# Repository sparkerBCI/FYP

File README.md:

# Brain Computer Interface Controlled, 3-D Printed Prosthetic Hand

This is an Electrical Engineering Final   Year Project by Samuel Parker, from the University of Newcastle.

### Scope
The project will attempt to conduct a real time frequency analysis of on-line EEG data. The frequency content will then be classified into "Hand Open" or "Hand Closed" using an appropriate classification algorithm. Once classified, the state will be used to control the servos in the 3D printed prosthetic hand. The goal of the project is to achieve realtime, neurally controlled grasping.

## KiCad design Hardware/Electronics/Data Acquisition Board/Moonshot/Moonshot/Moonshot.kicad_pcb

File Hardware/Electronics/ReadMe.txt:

A place to store electronics design files

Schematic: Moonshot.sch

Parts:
A1: Arduino_Nano_v2.x; Arduino_Nano
ADC1: ADS1299-Board
C1, C5: 10u; C_0603_1608Metric_Pad1.05x0.95mm_HandSolder
C2, C4: 1u; C_0603_1608Metric_Pad1.05x0.95mm_HandSolder
C3: 100n; C_0603_1608Metric_Pad1.05x0.95mm_HandSolder
D1: 7.5V; D_SMA_Handsoldering
J1: Barrel_Jack; BarrelJack_CUI_PJ-063AH_Horizontal
J2: Conn_01x06_Female; HC-05
J3, J4, J5, J6, J7, J8, J9, J10, J11: Conn_01x01_Male; DIN 42802-1
Q1: DMP2100U; SOT-23
R1: 33k; R_0603_1608Metric_Pad1.05x0.95mm_HandSolder
R2, R3, R4, R5: 1k; R_0603_1608Metric_Pad1.05x0.95mm_HandSolder
R6, R7, R8, R9: 2k; R_0603_1608Metric_Pad1.05x0.95mm_HandSolder
U2: MCP1755T-5002E_SOT223-5; SOT-223-6

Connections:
/+3V3: A1.17 (3V3), ADC1.5, ADC1.6
/+5V: C3.1, C4.1, C5.1, J2.5, U2.4
/BT_RX_3V3: A1.11 (D8), J2.3
/BT_TX_3V3: J2.2, R2.1, R6.1
/BT_TX_5V: A1.12 (D9), R2.2
/GND: A1.4 (GND), A1.29 (GND), ADC1.2, ADC1.8, C1.2, C2.2, C3.2, C4.2, C5.2, J1.2, J2.4, R1.2, R6.2, R7.2, R8.2, R9.2, U2.3, U2.5, U2.6
/LED: A1.6 (D3)
/MISO_3V3: A1.15 (D12), ADC1.11
/MOSI_3V3: ADC1.4, R4.1, R8.1
/MOSI_5V: A1.14 (D11), R4.2
/SCLK_3V3: ADC1.10, R3.1, R7.1
/SCLK_5V: A1.16 (D13), R3.2
/V+: A1.30 (VIN), ADC1.1, C1.1, C2.1, D1.1, Q1.2, U2.1, U2.2
/~CS_3V3: ADC1.9, R5.1, R9.1
/~CS_5V: A1.7 (D4), R5.2
/~DRDY_3V3: A1.9 (D6), ADC1.12
unnamed: ADC1.21, J11.1
unnamed: ADC1.22, J10.1
unnamed: ADC1.23, J9.1
unnamed: ADC1.24, J8.1
unnamed: ADC1.25, J7.1
unnamed: ADC1.26, J6.1
unnamed: ADC1.27, J5.1
unnamed: ADC1.28, J4.1
unnamed: ADC1.29, J3.1
unnamed: D1.2, Q1.1, R1.1
unnamed: J1.1, Q1.3

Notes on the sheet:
LED
GND
+5V
STATE

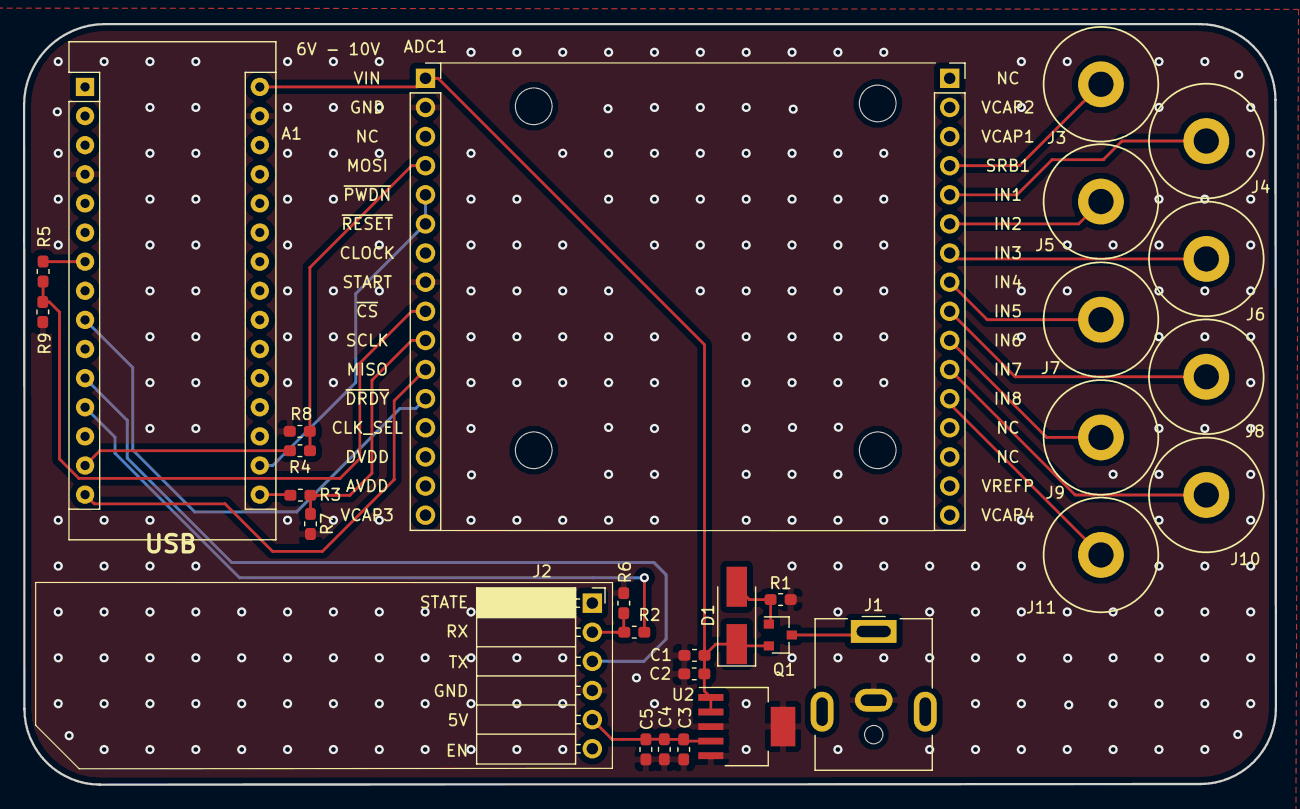
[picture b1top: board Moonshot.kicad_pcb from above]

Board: 2 copper layers, 109.2 x 66.3 mm, 34 parts (0 on the bottom side), 26 nets.

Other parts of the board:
 : MountingHole_3.2mm_M3
 #2,  #3,  #4: MountingHole_3.2mm_M3

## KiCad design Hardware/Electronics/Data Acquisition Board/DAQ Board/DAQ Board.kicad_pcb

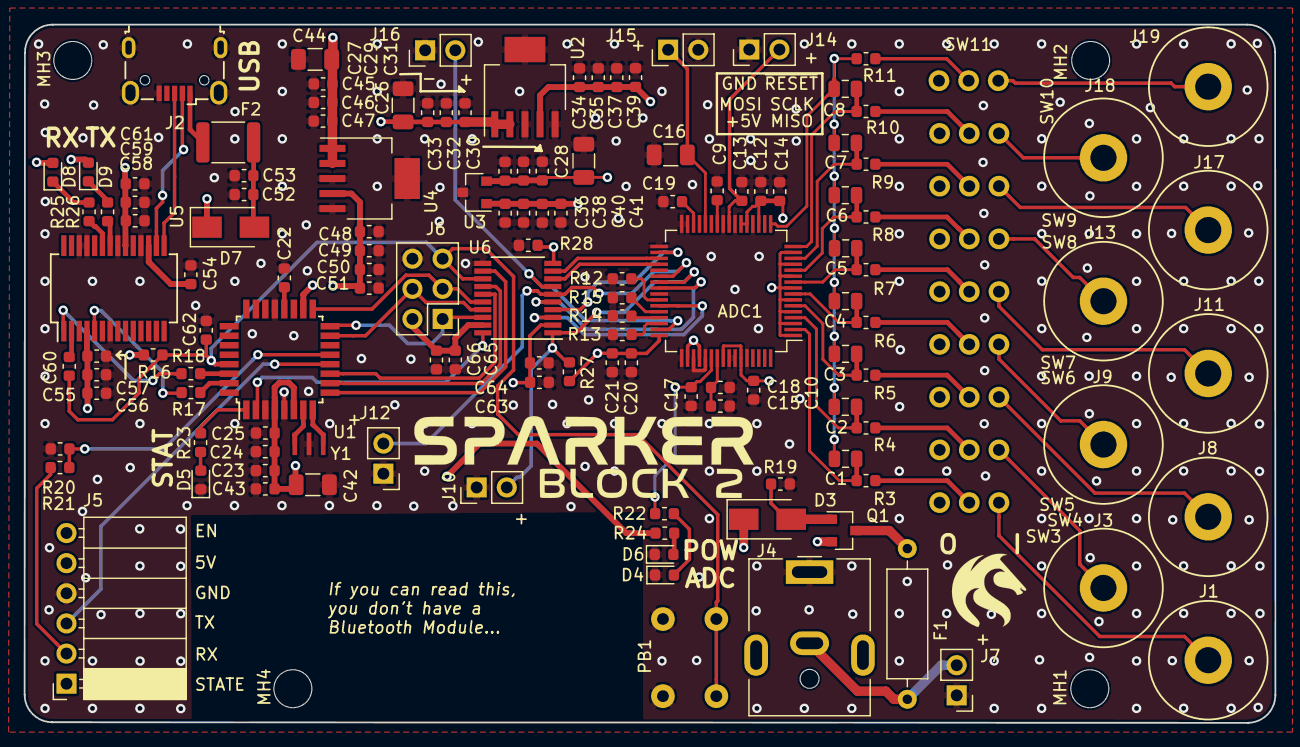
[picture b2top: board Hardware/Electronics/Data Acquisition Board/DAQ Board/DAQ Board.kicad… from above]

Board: 4 copper layers, 105.4 x 58.9 mm, 145 parts (0 on the bottom side), 84 nets.

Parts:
ADC1: ADS1299-8; TQFP-64_10x10mm_P0.5mm
C1, C2, C3, C4, C5, C6, C7, C8: 24nF; C_0805_2012Metric
C9, C10, C14, C17, C18, C19, C21, C23, C25: 1uF; C_0603_1608Metric
C12, C15, C20: 0.1uF; C_0603_1608Metric
C13, C27, C30, C39, C41, C43, C45, C51, C55, C61, C62: 10uF; C_0603_1608Metric
C16, C26, C28, C42, C44: 100uF; C_1206_3216Metric
C22, C29, C32, C37, C40, C46, C50, C53, C54, C56, C59, C60: 100nF; C_0603_1608Metric
C24, C52: 4.7uF; C_0603_1608Metric
C31, C33, C35, C38, C47, C49, C57, C58: 10nF; C_0603_1608Metric
C34, C36, C48: 1nF; C_0603_1608Metric
C63, C66: 100n; C_0603_1608Metric
C64, C65: 10n; C_0603_1608Metric
D3: 7.5V; D_SMA
D4, D6: LTST-C194TBKT; LED_0603_1608Metric
D5, D9: LTST-C191KGKT; LED_0603_1608Metric
D7: B130-13-F; D_SMA
D8: LTST-C191KRKT; LED_0603_1608Metric
F1: 025101.5MAT1L; R_Axial_DIN0309_L9.0mm_D3.2mm_P12.70mm_Horizontal
F2: MF-MSMF050-2; Fuse_1812_4532Metric
J1, J3, J8, J9, J11, J13, J17, J18, J19: Conn_01x01_Male; DIN 42802-1
J2: USB_B_Mini; USB_Micro-B_Wuerth_629105150521
J4: DC Barrel Jack; BarrelJack_CUI_PJ-063AH_Horizontal
J5: HC-05 BT Module; HC-05
J6: ICSP Header; PinHeader_2x03_P2.54mm_Vertical
J7: VIN_RAW_TP; PinHeader_1x02_P2.54mm_Vertical
J10: ~CS~_TP; PinHeader_1x02_P2.54mm_Vertical
J12: START_TP; PinHeader_1x02_P2.54mm_Vertical
J14: VREFP_TP; PinHeader_1x02_P2.54mm_Vertical
J15: VCAP1_TP; PinHeader_1x02_P2.54mm_Vertical
J16: DRDY_TP; PinHeader_1x02_P2.54mm_Vertical
LOGO1: UoNLogo; UoN
LOGO2: SparkerLogo; NASA
LOGO3: VersionLogo; Block2
MH1, MH2, MH3, MH4: MountingHole; MountingHole_3.2mm_M3
PB1: TE-1825910-6; 1825910-6
Q1: DMP2100U; SOT-23
R3, R4, R5, R6, R7, R8, R9, R10, R11: 220k; R_0603_1608Metric
R12, R13, R14, R15, R19: 33k; R_0603_1608Metric
R16, R17, R18, R21: 1K; R_0603_1608Metric
R20: 2K; R_0603_1608Metric
R22, R23, R24, R25, R26: 100; R_0603_1608Metric
R27, R28: 100k; R_0603_1608Metric
SW3, SW4, SW5, SW6, SW7, SW8, SW9, SW10, SW11: SW_SPDT; SPDT-THT_Slide
U1: ATmega328P-AU; TQFP-32_7x7mm_P0.8mm
U2, U4: MCP1755T-5002E_SOT223-5; SOT-223-6
U3: LM3480-3.3; SOT-23
U5: FT232RL; SSOP-28_5.3x10.2mm_P0.65mm
U6: TXS0108EPWR; TSSOP-20_4.4x6.5mm_P0.65mm
Y1: 16MHz; CSTNE16M0V53Z000R0

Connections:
/+3V3: ADC1.48, ADC1.50, ADC1.52, C20.1, C21.1, C36.1, C38.1, C40.1, C41.1, C63.1, C64.1, R27.1, R28.1, U3.1, U6.2, U6.10
/+5V: C23.1, C24.1, C25.1, C42.1, C43.1, C48.1, C49.1, C50.1, C51.1, C55.1, C56.1, C57.1, C58.1, C59.1, C61.1, C65.1, C66.1, D7.1, D8.2, D9.2, J5.5, J6.2, R16.1, R24.2, U1.4, U1.6, U1.18, U4.4, U5.4, U5.20, U6.19
/ADC1299/AVDD: ADC1.1, ADC1.3, ADC1.5, ADC1.7, ADC1.9, ADC1.11, ADC1.13, ADC1.15, ADC1.19, ADC1.21, ADC1.22, ADC1.54, ADC1.56, ADC1.59, C10.1, C12.2, C14.2, C17.2, C28.1, C30.1, C32.1, C33.1, C34.1, C35.1, C37.1, C39.1, R22.2, SW3.1, SW4.1, SW5.1, SW6.1, SW7.1, SW8.1, SW9.1, SW10.1, SW11.1, U2.4, U3.2
/ADC1299/VCAP1: ADC1.28, C16.1, J15.1
/ADC1299/VREFP: ADC1.24, C13.2, J14.2
/Arduino Nano/+3V3: C54.1, U5.17
/Arduino Nano/RX: R18.1, U5.1
/Arduino Nano/SS_TX: R20.1, R21.2, U1.13
/Arduino Nano/TX: R17.1, U5.5
/Arduino Nano/VUSB: C52.1, C53.1, D7.2, F2.1
/GND: ADC1.20, ADC1.23, ADC1.25, ADC1.31, ADC1.32, ADC1.33, ADC1.41, ADC1.49, ADC1.51, ADC1.53, ADC1.57, ADC1.58, ADC1.60, C9.2, C10.2, C12.1, C13.1, C14.1, C15.1, C16.2, C17.1, C18.1, C19.2, C20.2, C21.2, C22.2, C23.2, C24.2, C25.2, C26.2, C27.2, C28.2, C29.2, C30.2, C31.2, C32.2, C33.2, C34.2, C35.2, C36.2, C37.2, C38.2, C39.2, C40.2, C41.2, C42.2, C43.2, C44.2, C45.2, C46.2, C47.2, C48.2, C49.2, C50.2, C51.2, C52.2, C53.2, C54.2, C55.2, C56.2, C57.2, C58.2, C59.2, C61.2, C62.2, C63.2, C64.2, C65.2, C66.2, D4.1, D5.1, D6.1, J2.5, J2.6, J4.1, J5.4, J6.6, J7.1, J10.1, J12.1, J14.1, J15.2, J16.1, PB1.1, PB1.2, R12.2, R13.1, R14.1, R15.1, R19.2, R20.2, R28.2, U1.3, U1.5, U1.21, U2.3, U2.5, U2.6, U3.3, U4.3, U4.5, U4.6, U5.7, U5.18, U5.21, U5.25, U5.26, U6.11, Y1.2
/HC05_RX: J5.3, U1.12
/HC05_TX: J5.2, R21.1
/MISO_3V3: ADC1.43, U6.3
/MISO_5V: J6.1, U1.16, U6.18
/MOSI_3V3: ADC1.34, U6.4
/MOSI_5V: J6.4, U1.15, U6.17
/SCLK_3V3: ADC1.40, U6.5
/SCLK_5V: J6.3, U1.17, U6.16
/START_3V3: ADC1.38, J12.2, U6.6
/START_5V: U1.11, U6.15
/VIN: C26.1, C27.1, C29.1, C31.1, C44.1, C45.1, C46.1, C47.1, D3.1, Q1.2, U2.1, U2.2, U4.1, U4.2
/VIN_RAW: F1.2, J4.2, J7.2
/~CS_3V3: ADC1.39, J10.2, R27.2, U6.1
/~CS_5V: U1.2, U6.20
/~DRDY_3V3: ADC1.47, J16.2, U6.7
/~DRDY_5V: U1.10, U6.14
/~PWDN_3V3: ADC1.35, U6.9
/~PWDN_5V: U1.9, U6.12
/~RESET_3V3: ADC1.36, U6.8
/~RESET_5V: C60.2, C62.1, J6.5, PB1.3, PB1.4, R16.2, U1.29, U6.13
unnamed: ADC1.2, C1.1, R3.1
unnamed: ADC1.4, C2.1, R4.1
unnamed: ADC1.6, C3.1, R5.1
unnamed: ADC1.8, C4.1, R6.1
unnamed: ADC1.10, C5.1, R7.1
unnamed: ADC1.12, C6.1, R8.1
unnamed: ADC1.14, C7.1, R9.1
unnamed: ADC1.16, C8.1, R10.1
unnamed: ADC1.17, C1.2, C2.2, C3.2, C4.2, C5.2, C6.2, C7.2, C8.2, R11.1
unnamed: ADC1.26, C9.1
unnamed: ADC1.30, C19.1
unnamed: ADC1.42, R12.1
unnamed: ADC1.44, R15.2
unnamed: ADC1.45, R14.2
unnamed: ADC1.46, R13.2
unnamed: ADC1.55, C15.2, C18.2
unnamed: C22.1, U1.20
unnamed: C60.1, U5.2
unnamed: D3.2, Q1.1, R19.1
unnamed: D4.2, R22.1
unnamed: D5.2, R23.1
unnamed: D6.2, R24.1
unnamed: D8.1, R25.1
unnamed: D9.1, R26.1
unnamed: F1.1, Q1.3
unnamed: F2.2, J2.1
unnamed: J1.1, SW3.3
unnamed: J2.2, U5.16
unnamed: J2.3, U5.15
unnamed: J3.1, SW4.3
unnamed: J8.1, SW5.3
unnamed: J9.1, SW6.3
unnamed: J11.1, SW7.3
unnamed: J13.1, SW8.3
unnamed: J17.1, SW9.3
unnamed: J18.1, SW10.3
unnamed: J19.1, SW11.3
unnamed: R3.2, SW3.2
unnamed: R4.2, SW4.2
unnamed: R5.2, SW5.2
unnamed: R6.2, SW6.2
unnamed: R7.2, SW7.2
unnamed: R8.2, SW8.2
unnamed: R9.2, SW9.2
unnamed: R10.2, SW10.2
unnamed: R11.2, SW11.2
unnamed: R17.2, U1.31
unnamed: R18.2, U1.30
unnamed: R23.2, U1.1
unnamed: R25.2, U5.23
unnamed: R26.2, U5.22
unnamed: U1.7, Y1.3
unnamed: U1.8, Y1.1

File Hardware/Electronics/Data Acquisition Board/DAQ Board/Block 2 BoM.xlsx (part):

| Ref | Value | Package | Price | SMD | THT | Notes | Digikey Part # | URL
 | ADC1 | ADS1299-8 | Package_QFP:TQFP-64_10x10mm_P0.5mm | 0 | 1 | 0 | Usual Price $86.98. 8 Channel AFE 24 Bit 42mW 64-TQFP (10x10) | 296-34818-1-ND | https://www.digikey.com.au/product-detail/en/texas-instrumen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
 | C1 | 24nF | Capacitor_SMD:C_0805_2012Metric | 0.82 | 1 | 0 | 0.022µF ±5% 50V Ceramic Capacitor C0G, NP0 0805 (2012 Metric) | 490-1644-1-ND | https://www.digikey.com.au/product-detail/en/murata-electron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
 | C2 | 24nF | Capacitor_SMD:C_0805_2012Metric | 0.82 | 1 | 0 | 0.022µF ±5% 50V Ceramic Capacitor C0G, NP0 0805 (2012 Metric) | 490-1644-1-ND | https://www.digikey.com.au/product-detail/en/murata-electron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
 | C3 | 24nF | Capacitor_SMD:C_0805_2012Metric | 0.82 | 1 | 0 | 0.022µF ±5% 50V Ceramic Capacitor C0G, NP0 0805 (2012 Metric) | 490-1644-1-ND | https://www.digikey.com.au/product-detail/en/murata-electron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
 | C4 | 24nF | Capacitor_SMD:C_0805_2012Metric | 0.82 | 1 | 0 | 0.022µF ±5% 50V Ceramic Capacitor C0G, NP0 0805 (2012 Metric) | 490-1644-1-ND | https://www.digikey.com.au/product-detail/en/murata-electron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
 | C5 | 24nF | Capacitor_SMD:C_0805_2012Metric | 0.82 | 1 | 0 | 0.022µF ±5% 50V Ceramic Capacitor C0G, NP0 0805 (2012 Metric) | 490-1644-1-ND | https://www.digikey.com.au/product-detail/en/murata-electron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
 | C6 | 24nF | Capacitor_SMD:C_0805_2012Metric | 0.82 | 1 | 0 | 0.022µF ±5% 50V Ceramic Capacitor C0G, NP0 0805 (2012 Metric) | 490-1644-1-ND | https://www.digikey.com.au/product-detail/en/murata-electron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
 | C7 | 24nF | Capacitor_SMD:C_0805_2012Metric | 0.82 | 1 | 0 | 0.022µF ±5% 50V Ceramic Capacitor C0G, NP0 0805 (2012 Metric) | 490-1644-1-ND | https://www.digikey.com.au/product-detail/en/murata-electron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
 | C8 | 24nF | Capacitor_SMD:C_0805_2012Metric | 0.82 | 1 | 0 | 0.022µF ±5% 50V Ceramic Capacitor C0G, NP0 0805 (2012 Metric) | 490-1644-1-ND | https://www.digikey.com.au/product-detail/en/murata-electron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
 | C9 | 1uF | Capacitor_SMD:C_0603_1608Metric | 0.17 | 1 | 0 | 1µF ±20% 16V Ceramic Capacitor X7R 0603 (1608 Metric) | 1276-6524-1-ND | https://www.digikey.com.au/product-detail/en/CL10B105MO8NNWC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
 | C10 | 1uF | Capacitor_SMD:C_0603_1608Metric | 0.17 | 1 | 0 | 1µF ±20% 16V Ceramic Capacitor X7R 0603 (1608 Metric) | 1276-6524-1-ND | https://www.digikey.com.au/product-detail/en/CL10B105MO8NNWC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
 | C12 | 0.1uF | Capacitor_SMD:C_0603_1608Metric | 0.17 | 1 | 0 | 0.1µF ±10% 50V Ceramic Capacitor X7R 0603 (1608 Metric) | 1276-CL10B104KB8NNNLCT-ND | https://www.digikey.com.au/product-detail/en/CL10B104KB8NNNL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
 | C13 | 10uF | Capacitor_SMD:C_0603_1608Metric | 0 | 1 | 0
 | C14 | 1uF | Capacitor_SMD:C_0603_1608Metric | 0.17 | 1 | 0 | 1µF ±20% 16V Ceramic Capacitor X7R 0603 (1608 Metric) | 1276-6524-1-ND | https://www.digikey.com.au/product-detail/en/CL10B105MO8NNWC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
 | C15 | 0.1uF | Capacitor_SMD:C_0603_1608Metric | 0.17 | 1 | 0 | 0.1µF ±10% 50V Ceramic Capacitor X7R 0603 (1608 Metric) | 1276-CL10B104KB8NNNLCT-ND | https://www.digikey.com.au/product-detail/en/CL10B104KB8NNNL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
 | C16 | 100uF | Capacitor_SMD:C_1206_3216Metric | 2.6 | 1 | 0 | 100µF ±20% 10V Ceramic Capacitor X5R 1206 (3216 Metric) | 445-6007-1-ND | https://www.digikey.com.au/product-detail/en/tdk-corporation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
 | C17 | 1uF | Capacitor_SMD:C_0603_1608Metric | 0.17 | 1 | 0 | 1µF ±20% 16V Ceramic Capacitor X7R 0603 (1608 Metric) | 1276-6524-1-ND | https://www.digikey.com.au/product-detail/en/CL10B105MO8NNWC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
 | C18 | 1uF | Capacitor_SMD:C_0603_1608Metric | 0.17 | 1 | 0 | 1µF ±20% 16V Ceramic Capacitor X7R 0603 (1608 Metric) | 1276-6524-1-ND | https://www.digikey.com.au/product-detail/en/CL10B105MO8NNWC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
 | C19 | 1uF | Capacitor_SMD:C_0603_1608Metric | 0.17 | 1 | 0 | 1µF ±20% 16V Ceramic Capacitor X7R 0603 (1608 Metric) | 1276-6524-1-ND | https://www.digikey.com.au/product-detail/en/CL10B105MO8NNWC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
 | C20 | 0.1uF | Capacitor_SMD:C_0603_1608Metric | 0.17 | 1 | 0 | 0.1µF ±10% 50V Ceramic Capacitor X7R 0603 (1608 Metric) | 1276-CL10B104KB8NNNLCT-ND | https://www.digikey.com.au/product-detail/en/CL10B104KB8NNNL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
 | C21 | 1uF | Capacitor_SMD:C_0603_1608Metric | 0.17 | 1 | 0 | 1µF ±20% 16V Ceramic Capacitor X7R 0603 (1608 Metric) | 1276-6524-1-ND | https://www.digikey.com.au/product-detail/en/CL10B105MO8NNWC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
 | C22 | 100nF | Capacitor_SMD:C_0603_1608Metric | 0.17 | 1 | 0 | 0.1µF ±10% 50V Ceramic Capacitor X7R 0603 (1608 Metric) | 1276-CL10B104KB8NNNLCT-ND | https://www.digikey.com.au/product-detail/en/CL10B104KB8NNNL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
 | C23 | 1uF | Capacitor_SMD:C_0603_1608Metric | 0.17 | 1 | 0 | 1µF ±20% 16V Ceramic Capacitor X7R 0603 (1608 Metric) | 1276-6524-1-ND | https://www.digikey.com.au/product-detail/en/CL10B105MO8NNWC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
 | C24 | 4.7uF | Capacitor_SMD:C_0603_1608Metric | 0 | 1 | 0
 | C25 | 1uF | Capacitor_SMD:C_0603_1608Metric | 0.17 | 1 | 0 | 1µF ±20% 16V Ceramic Capacitor X7R 0603 (1608 Metric) | 1276-6524-1-ND | https://www.digikey.com.au/product-detail/en/CL10B105MO8NNWC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
 | C26 | 100uF | Capacitor_SMD:C_1206_3216Metric | 2.6 | 1 | 0 | 100µF ±20% 10V Ceramic Capacitor X5R 1206 (3216 Metric) | 445-6007-1-ND | https://www.digikey.com.au/product-detail/en/tdk-corporation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
 | C27 | 10uF | Capacitor_SMD:C_0603_1608Metric | 0 | 1 | 0
 | C28 | 100uF | Capacitor_SMD:C_1206_3216Metric | 2.6 | 1 | 0 | 100µF ±20% 10V Ceramic Capacitor X5R 1206 (3216 Metric) | 445-6007-1-ND | https://www.digikey.com.au/product-detail/en/tdk-corporation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
 | C29 | 100nF | Capacitor_SMD:C_0603_1608Metric | 0.17 | 1 | 0 | 0.1µF ±10% 50V Ceramic Capacitor X7R 0603 (1608 Metric) | 1276-CL10B104KB8NNNLCT-ND | https://www.digikey.com.au/product-detail/en/CL10B104KB8NNNL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
 | C30 | 10uF | Capacitor_SMD:C_0603_1608Metric | 0 | 1 | 0
 | C31 | 10nF | Capacitor_SMD:C_0603_1608Metric | 0.17 | 1 | 0 | 10000pF ±10% 50V Ceramic Capacitor X7R 0603 (1608 Metric) | 445-5662-1-ND | https://www.digikey.com.au/product-detail/en/CGA3E2X7R1H103K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
 | C32 | 100nF | Capacitor_SMD:C_0603_1608Metric | 0.17 | 1 | 0 | 0.1µF ±10% 50V Ceramic Capacitor X7R 0603 (1608 Metric) | 1276-CL10B104KB8NNNLCT-ND | https://www.digikey.com.au/product-detail/en/CL10B104KB8NNNL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
 | C33 | 10nF | Capacitor_SMD:C_0603_1608Metric | 0.17 | 1 | 0 | 10000pF ±10% 50V Ceramic Capacitor X7R 0603 (1608 Metric) | 445-5662-1-ND | https://www.digikey.com.au/product-detail/en/CGA3E2X7R1H103K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
 | C34 | 1nF | Capacitor_SMD:C_0603_1608Metric | 0 | 1 | 0
 | C35 | 10nF | Capacitor_SMD:C_0603_1608Metric | 0.17 | 1 | 0 | 10000pF ±10% 50V Ceramic Capacitor X7R 0603 (1608 Metric) | 445-5662-1-ND | https://www.digikey.com.au/product-detail/en/CGA3E2X7R1H103K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
 | C36 | 1nF | Capacitor_SMD:C_0603_1608Metric | 0 | 1 | 0
 | C37 | 100nF | Capacitor_SMD:C_0603_1608Metric | 0.17 | 1 | 0 | 0.1µF ±10% 50V Ceramic Capacitor X7R 0603 (1608 Metric) | 1276-CL10B104KB8NNNLCT-ND | https://www.digikey.com.au/product-detail/en/CL10B104KB8NNNL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
 | C38 | 10nF | Capacitor_SMD:C_0603_1608Metric | 0.17 | 1 | 0 | 10000pF ±10% 50V Ceramic Capacitor X7R 0603 (1608 Metric) | 445-5662-1-ND | https://www.digikey.com.au/product-detail/en/CGA3E2X7R1H103K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
 | C39 | 10uF | Capacitor_SMD:C_0603_1608Metric | 0 | 1 | 0
 | C40 | 100nF | Capacitor_SMD:C_0603_1608Metric | 0.17 | 1 | 0 | 0.1µF ±10% 50V Ceramic Capacitor X7R 0603 (1608 Metric) | 1276-CL10B104KB8NNNLCT-ND | https://www.digikey.com.au/product-detail/en/CL10B104KB8NNNL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
 | C41 | 10uF | Capacitor_SMD:C_0603_1608Metric | 0 | 1 | 0
 | C42 | 100uF | Capacitor_SMD:C_1206_3216Metric | 2.6 | 1 | 0 | 100µF ±20% 10V Ceramic Capacitor X5R 1206 (3216 Metric) | 445-6007-1-ND | https://www.digikey.com.au/product-detail/en/tdk-corporation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
 | C43 | 10uF | Capacitor_SMD:C_0603_1608Metric | 0.28000000000000003 | 1 | 0 | 10µF ±20% 6.3V Ceramic Capacitor X5R 0603 (1608 Metric) | 1276-1119-1-ND | https://www.digikey.com.au/product-detail/en/samsung-electro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
 | C44 | 100uF | Capacitor_SMD:C_1206_3216Metric | 2.6 | 1 | 0 | 100µF ±20% 10V Ceramic Capacitor X5R 1206 (3216 Metric) | 445-6007-1-ND | https://www.digikey.com.au/product-detail/en/tdk-corporation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

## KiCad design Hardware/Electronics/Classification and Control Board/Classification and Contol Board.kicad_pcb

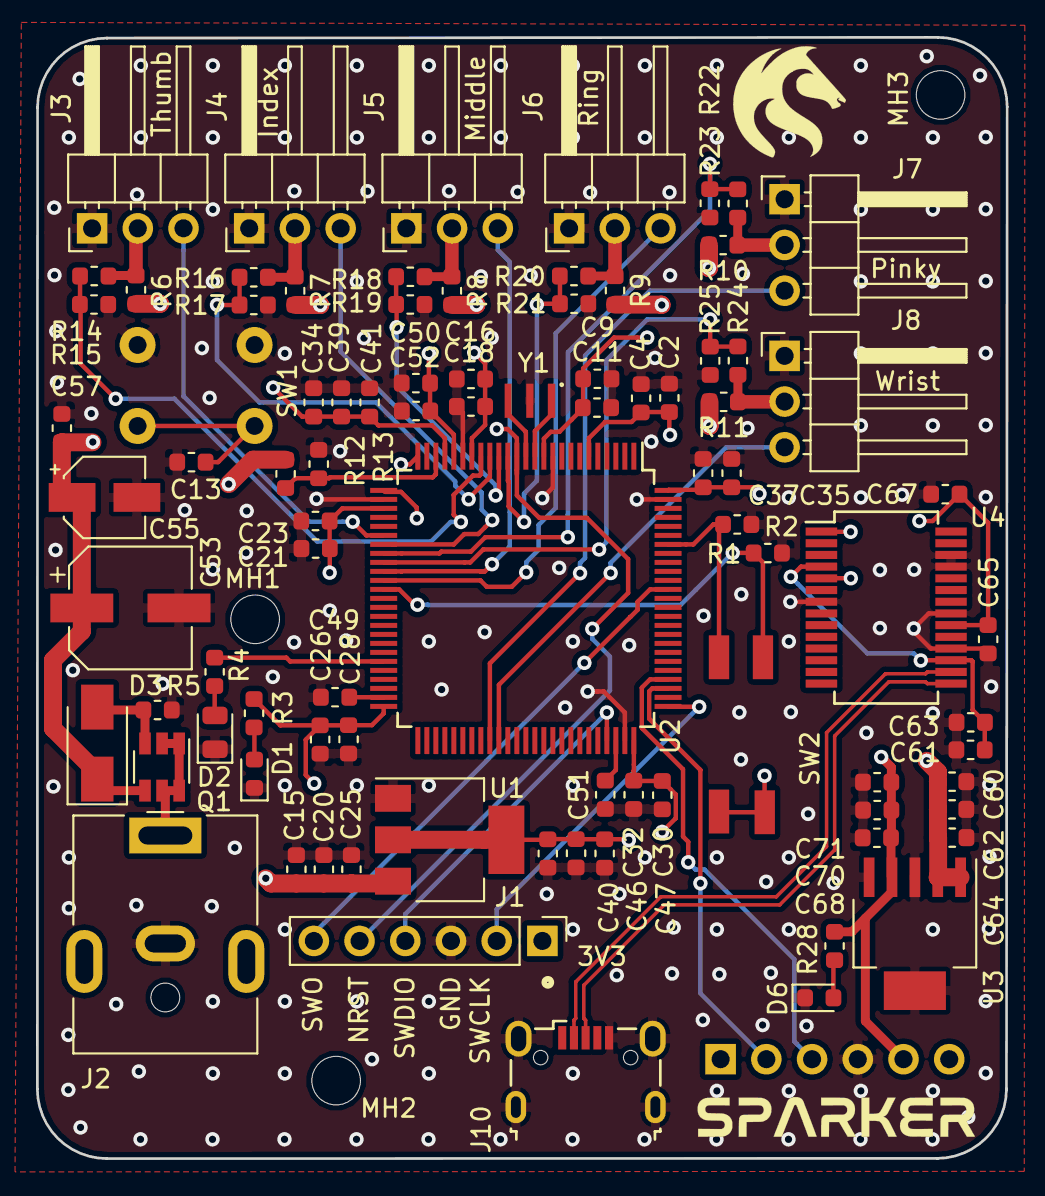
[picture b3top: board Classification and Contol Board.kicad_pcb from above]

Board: 4 copper layers, 53.9 x 62.3 mm, 94 parts (1 on the bottom side), 46 nets.

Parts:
C2, C9, C16, C21, C26, C30, C35, C39, C61, C62, C67, C70: 100n; C_0603_1608Metric
C4, C11, C18, C20, C23, C28, C32, C34, C37, C46, C52, C63, C64, C65, C71: 10n; C_0603_1608Metric
C13: 0.1u; C_0603_1608Metric
C15, C47, C57, C60, C68: 4.7u; C_0603_1608Metric
C25, C40: 1n; C_0603_1608Metric
C41, C50: 1u; C_0603_1608Metric
C49, C51: 2.2u; C_0603_1608Metric
C53: 100u; CP_Elec_6.3x7.7
C55: 10u; CP_Elec_4x5.4
D1: LTST-C171TGKT; LED_0603_1608Metric
D2: LO R976-PS-1; LED_0805_2012Metric
D3: 10V; D_SMA
D6: LED; LED_0603_1608Metric
J1: SWD Header; PinHeader_1x06_P2.54mm_Vertical
J2: Barrel_Jack; BarrelJack_CUI_PJ-063AH_Horizontal
J3: Thumb; PinHeader_1x03_P2.54mm_Horizontal
J4: Index; PinHeader_1x03_P2.54mm_Horizontal
J5: Middle; PinHeader_1x03_P2.54mm_Horizontal
J6: Ring; PinHeader_1x03_P2.54mm_Horizontal
J7: Pinky; PinHeader_1x03_P2.54mm_Horizontal
J8: Wrist; PinHeader_1x03_P2.54mm_Horizontal
J9: HC05; HC-05
J10: USB_B_Mini; USB_Micro-B_Wuerth_629105150521
LOGO1: SparkerLogo; NASA_small
LOGO2: UoNLogo; UoN
MH1, MH2, MH3: MountingHole; MountingHole_2.7mm_M2.5
Q1: SQ3425EV-T1_GE3; TSOT-23-6
R1, R2, R13, R15, R17, R19, R21, R23, R25: 100k; R_0603_1608Metric
R3: 6R; R_0603_1608Metric
R4: 68R; R_0603_1608Metric
R5: 33k; R_0603_1608Metric
R6, R7, R8, R9, R10, R11: 50m; R_0603_1608Metric
R12, R14, R16, R18, R20, R22, R24: 500k; R_0603_1608Metric
R28: 150; R_0603_1608Metric
SW1: SW_Push; 1825910-6
SW2: SW_DIP_x02; DIP-Switch_01x02
U1: LDL1117S33R; SOT-223-3_TabPin2
U2: STM32F407VGTx; LQFP-100_14x14mm_P0.5mm
U3: MCP1755T-5002E_SOT223-5; SOT-223-6
U4: FT232RL; SSOP-28_5.3x10.2mm_P0.65mm
Y1: 8MHz; CSTNE12M0GH5L000R0

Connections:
/Communications/+5V: C65.1, C67.1, C68.1, C70.1, C71.1, J9.5, R28.2, U3.4, U4.20
/Communications/BT_RX: J9.3, U2.79
/Communications/BT_TX: J9.2, U2.78
/Communications/D+: J10.3, U4.15
/Communications/D-: J10.2, U4.16
/Communications/RX: U2.26, U4.5
/Communications/TX: U2.25, U4.1
/Control/FB1: R14.2, R15.1, U2.18
/Control/FB2: R16.2, R17.1, U2.17
/Control/FB3: R18.2, R19.1, U2.16
/Control/FB4: R20.2, R21.1, U2.15
/Control/FB5: R22.2, R23.1, U2.33
/Control/FB6: R24.2, R25.1, U2.34
/Control/FB_REF: R12.2, R13.1, U2.23
/Control/VSER1: J3.2, R6.1, R14.1
/Control/VSER2: J4.2, R7.1, R16.1
/Control/VSER3: J5.2, R8.1, R18.1
/Control/VSER4: J6.2, R9.1, R20.1
/Control/VSER5: J7.2, R10.1, R22.1
/Control/VSER6: J8.2, R11.1, R24.1
/GND: C2.2, C4.2, C9.2, C11.2, C13.2, C15.2, C16.2, C18.2, C20.2, C21.2, C23.2, C25.2, C26.2, C28.2, C30.2, C32.2, C34.2, C35.2, C37.2, C39.2, C40.2, C41.2, C46.2, C47.2, C49.2, C50.2, C51.2, C52.2, C53.2, C55.2, C57.2, C60.2, C61.2, C62.2, C63.2, C64.2, C65.2, C67.2, C68.2, C70.2, C71.2, D1.1, D2.1, D6.1, J1.3, J2.2, J3.1, J4.1, J5.1, J6.1, J7.1, J8.1, J9.4, J10.5, J10.6, R1.2, R2.2, R5.2, R13.2, R15.2, R17.2, R19.2, R21.2, R23.2, R25.2, SW1.1, SW1.2, U1.1, U2.10, U2.20, U2.27, U2.74, U2.99, U3.3, U3.5, U3.6, U4.7, U4.18, U4.21, U4.25, U4.26, Y1.2
/STM32F407VGTx/3V3: C2.1, C4.1, C9.1, C11.1, C16.1, C18.1, C21.1, C23.1, C26.1, C28.1, C30.1, C32.1, C34.1, C35.1, C37.1, C39.1, C40.1, C41.1, C46.1, C47.1, C50.1, C52.1, J1.1, R3.2, SW2.3, SW2.4, U1.2, U2.6, U2.11, U2.19, U2.21, U2.22, U2.28, U2.50, U2.75, U2.100
/STM32F407VGTx/BOOT0: R1.1, SW2.2, U2.94
/STM32F407VGTx/BOOT1: R2.1, SW2.1, U2.37
/STM32F407VGTx/NRST: C13.1, J1.5, SW1.3, SW1.4, U2.14
/STM32F407VGTx/PWM1: J3.3, U2.31
/STM32F407VGTx/PWM2: J4.3, U2.32
/STM32F407VGTx/PWM3: J5.3, U2.35
/STM32F407VGTx/PWM4: J6.3, U2.36
/STM32F407VGTx/PWM5: J7.3, U2.59
/STM32F407VGTx/PWM6: J8.3, U2.60
/STM32F407VGTx/SWCLK: J1.2, U2.76
/STM32F407VGTx/SWDIO: J1.4, U2.72
/STM32F407VGTx/SWO: J1.6, U2.89
/V+: C15.1, C20.1, C25.1, C53.1, C55.1, C57.1, C60.1, C62.1, C64.1, D3.1, Q1.4, R6.2, R7.2, R8.2, R9.2, R10.2, R11.2, R12.1, U1.3, U3.1, U3.2
unnamed: C49.1, U2.49
unnamed: C51.1, U2.73
unnamed: C61.1, C63.1, U4.4, U4.17
unnamed: D1.2, R3.1
unnamed: D2.2, R4.2
unnamed: D3.2, Q1.3, R5.1
unnamed: D6.2, R28.1
unnamed: J2.1, Q1.1, Q1.2, Q1.5, Q1.6
unnamed: R4.1, U2.45
unnamed: U2.12, Y1.1
unnamed: U2.13, Y1.3

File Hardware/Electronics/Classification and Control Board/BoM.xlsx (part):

| Ref | Value | Package | Price | SMD | THT | Notes | Digikey Part # | URL | Cart Line Item
 | C15 | 4.7u | Capacitor_SMD:C_0603_1608Metric | 0.63 | 1 | 0 | 4.7µF ±10% 25V Ceramic Capacitor X5R 0603 (1608 Metric) | 1276-1900-1-ND | https://www.digikey.com.au/product-detail/en/samsung-electro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 | 1
 | C47 | 4.7u | Capacitor_SMD:C_0603_1608Metric | 0.63 | 1 | 0 | 4.7µF ±10% 25V Ceramic Capacitor X5R 0603 (1608 Metric) | 1276-1900-1-ND | https://www.digikey.com.au/product-detail/en/samsung-electro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 | 1
 | C57 | 4.7u | Capacitor_SMD:C_0603_1608Metric | 0.63 | 1 | 0 | 4.7µF ±10% 25V Ceramic Capacitor X5R 0603 (1608 Metric) | 1276-1900-1-ND | https://www.digikey.com.au/product-detail/en/samsung-electro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 | 1
 | C60 | 4.7u | Capacitor_SMD:C_0603_1608Metric | 0.63 | 1 | 0 | 4.7µF ±10% 25V Ceramic Capacitor X5R 0603 (1608 Metric) | 1276-1900-1-ND | https://www.digikey.com.au/product-detail/en/samsung-electro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 | 1
 | C68 | 4.7u | Capacitor_SMD:C_0603_1608Metric | 0.63 | 1 | 0 | 4.7µF ±10% 25V Ceramic Capacitor X5R 0603 (1608 Metric) | 1276-1900-1-ND | https://www.digikey.com.au/product-detail/en/samsung-electro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 | 1
 | C41 | 1u | Capacitor_SMD:C_0603_1608Metric | 0.17 | 1 | 0 | 1µF ±20% 16V Ceramic Capacitor X7R 0603 (1608 Metric) | 1276-6524-1-ND | https://www.digikey.com.au/product-detail/en/samsung-electro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 | 2
 | C50 | 1u | Capacitor_SMD:C_0603_1608Metric | 0.17 | 1 | 0 | 1µF ±20% 16V Ceramic Capacitor X7R 0603 (1608 Metric) | 1276-6524-1-ND | https://www.digikey.com.au/product-detail/en/samsung-electro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 | 2
 | C2 | 100n | Capacitor_SMD:C_0603_1608Metric | 0.17 | 1 | 0 | 0.1µF ±10% 50V Ceramic Capacitor X7R 0603 (1608 Metric) | 1276-CL10B104KB8NNNLCT-ND | https://www.digikey.com.au/product-detail/en/samsung-electro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 | 3
 | C9 | 100n | Capacitor_SMD:C_0603_1608Metric | 0.17 | 1 | 0 | 0.1µF ±10% 50V Ceramic Capacitor X7R 0603 (1608 Metric) | 1276-CL10B104KB8NNNLCT-ND | https://www.digikey.com.au/product-detail/en/samsung-electro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 | 3
 | C13 | 0.1u | Capacitor_SMD:C_0603_1608Metric | 0.17 | 1 | 0 | 0.1µF ±10% 50V Ceramic Capacitor X7R 0603 (1608 Metric) | 1276-CL10B104KB8NNNLCT-ND | https://www.digikey.com.au/product-detail/en/samsung-electro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 | 3
 | C16 | 100n | Capacitor_SMD:C_0603_1608Metric | 0.17 | 1 | 0 | 0.1µF ±10% 50V Ceramic Capacitor X7R 0603 (1608 Metric) | 1276-CL10B104KB8NNNLCT-ND | https://www.digikey.com.au/product-detail/en/samsung-electro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 | 3
 | C21 | 100n | Capacitor_SMD:C_0603_1608Metric | 0.17 | 1 | 0 | 0.1µF ±10% 50V Ceramic Capacitor X7R 0603 (1608 Metric) | 1276-CL10B104KB8NNNLCT-ND | https://www.digikey.com.au/product-detail/en/samsung-electro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 | 3
 | C26 | 100n | Capacitor_SMD:C_0603_1608Metric | 0.17 | 1 | 0 | 0.1µF ±10% 50V Ceramic Capacitor X7R 0603 (1608 Metric) | 1276-CL10B104KB8NNNLCT-ND | https://www.digikey.com.au/product-detail/en/samsung-electro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 | 3
 | C30 | 100n | Capacitor_SMD:C_0603_1608Metric | 0.17 | 1 | 0 | 0.1µF ±10% 50V Ceramic Capacitor X7R 0603 (1608 Metric) | 1276-CL10B104KB8NNNLCT-ND | https://www.digikey.com.au/product-detail/en/samsung-electro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 | 3
 | C35 | 100n | Capacitor_SMD:C_0603_1608Metric | 0.17 | 1 | 0 | 0.1µF ±10% 50V Ceramic Capacitor X7R 0603 (1608 Metric) | 1276-CL10B104KB8NNNLCT-ND | https://www.digikey.com.au/product-detail/en/samsung-electro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 | 3
 | C39 | 100n | Capacitor_SMD:C_0603_1608Metric | 0.17 | 1 | 0 | 0.1µF ±10% 50V Ceramic Capacitor X7R 0603 (1608 Metric) | 1276-CL10B104KB8NNNLCT-ND | https://www.digikey.com.au/product-detail/en/samsung-electro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 | 3
 | C61 | 100n | Capacitor_SMD:C_0603_1608Metric | 0.17 | 1 | 0 | 0.1µF ±10% 50V Ceramic Capacitor X7R 0603 (1608 Metric) | 1276-CL10B104KB8NNNLCT-ND | https://www.digikey.com.au/product-detail/en/samsung-electro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 | 3
 | C62 | 100n | Capacitor_SMD:C_0603_1608Metric | 0.17 | 1 | 0 | 0.1µF ±10% 50V Ceramic Capacitor X7R 0603 (1608 Metric) | 1276-CL10B104KB8NNNLCT-ND | https://www.digikey.com.au/product-detail/en/samsung-electro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 | 3
 | C67 | 100n | Capacitor_SMD:C_0603_1608Metric | 0.17 | 1 | 0 | 0.1µF ±10% 50V Ceramic Capacitor X7R 0603 (1608 Metric) | 1276-CL10B104KB8NNNLCT-ND | https://www.digikey.com.au/product-detail/en/samsung-electro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 | 3
 | C70 | 100n | Capacitor_SMD:C_0603_1608Metric | 0.17 | 1 | 0 | 0.1µF ±10% 50V Ceramic Capacitor X7R 0603 (1608 Metric) | 1276-CL10B104KB8NNNLCT-ND | https://www.digikey.com.au/product-detail/en/samsung-electro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 | 3
 | D1 | LTST-C171TGKT | LED_SMD:LED_0805_2012Metric | 0.44 | 1 | 0 | Green 571nm LED Indication - Discrete 2V 0603 (1608 Metric) | 160-1446-1-ND | https://www.digikey.com.au/product-detail/en/lite-on-inc/LTS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 | 4
 | D6 | LTST-C171TGKT | LED_SMD:LED_0805_2012Metric | 0.44 | 1 | 0 | Green 571nm LED Indication - Discrete 2V 0603 (1608 Metric) | 160-1446-1-ND | https://www.digikey.com.au/product-detail/en/lite-on-inc/LTS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 | 4
 | R6 | 50m | Resistor_SMD:R_0603_1608Metric | 0.68 | 1 | 0 | 50 mOhms ±0.5% 0.2W, 1/5W Chip Resistor 0603 (1608 Metric) Current Sense Metal 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 | 273-KDV06DR050ETCT-ND | https://www.digikey.com.au/product-detail/en/ohmite/KDV06DR0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 | 5
 | R7 | 50m | Resistor_SMD:R_0603_1608Metric | 0.68 | 1 | 0 | 50 mOhms ±0.5% 0.2W, 1/5W Chip Resistor 0603 (1608 Metric) Current Sense Metal 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 | 273-KDV06DR050ETCT-ND | https://www.digikey.com.au/product-detail/en/ohmite/KDV06DR0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 | 5
 | R8 | 50m | Resistor_SMD:R_0603_1608Metric | 0.68 | 1 | 0 | 50 mOhms ±0.5% 0.2W, 1/5W Chip Resistor 0603 (1608 Metric) Current Sense Metal 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 | 273-KDV06DR050ETCT-ND | https://www.digikey.com.au/product-detail/en/ohmite/KDV06DR0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 | 5
 | R9 | 50m | Resistor_SMD:R_0603_1608Metric | 0.68 | 1 | 0 | 50 mOhms ±0.5% 0.2W, 1/5W Chip Resistor 0603 (1608 Metric) Current Sense Metal 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 | 273-KDV06DR050ETCT-ND | https://www.digikey.com.au/product-detail/en/ohmite/KDV06DR0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 | 5
 | R10 | 50m | Resistor_SMD:R_0603_1608Metric | 0.68 | 1 | 0 | 50 mOhms ±0.5% 0.2W, 1/5W Chip Resistor 0603 (1608 Metric) Current Sense Metal 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 | 273-KDV06DR050ETCT-ND | https://www.digikey.com.au/product-detail/en/ohmite/KDV06DR0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 | 5
 | R11 | 50m | Resistor_SMD:R_0603_1608Metric | 0.68 | 1 | 0 | 50 mOhms ±0.5% 0.2W, 1/5W Chip Resistor 0603 (1608 Metric) Current Sense Metal 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 | 273-KDV06DR050ETCT-ND | https://www.digikey.com.au/product-detail/en/ohmite/KDV06DR0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 | 5
 | C25 | 1n | Capacitor_SMD:C_0603_1608Metric | 0.17 | 1 | 0 | 1000pF ±10% 50V Ceramic Capacitor X7R 0603 (1608 Metric) | 311-1080-1-ND | https://www.digikey.com.au/product-detail/en/yageo/CC0603KRX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 | 6
 | C40 | 1n | Capacitor_SMD:C_0603_1608Metric | 0.17 | 1 | 0 | 1000pF ±10% 50V Ceramic Capacitor X7R 0603 (1608 Metric) | 311-1080-1-ND | https://www.digikey.com.au/product-detail/en/yageo/CC0603KRX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 | 6
 | C49 | 2.2u | Capacitor_SMD:C_0603_1608Metric | 0.24 | 1 | 0 | 2.2µF ±10% 16V Ceramic Capacitor X5R 0603 (1608 Metric) | 399-7886-1-ND | https://www.digikey.com.au/product-detail/en/kemet/C0603C225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 | 7
 | C51 | 2.2u | Capacitor_SMD:C_0603_1608Metric | 0.24 | 1 | 0 | 2.2µF ±10% 16V Ceramic Capacitor X5R 0603 (1608 Metric) | 399-7886-1-ND | https://www.digikey.com.au/product-detail/en/kemet/C0603C225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 | 7
 | C4 | 10n | Capacitor_SMD:C_0603_1608Metric | 0.17 | 1 | 0 | 10000pF ±10% 50V Ceramic Capacitor X7R 0603 (1608 Metric) | 445-5662-1-ND | https://www.digikey.com.au/product-detail/en/tdk-corporation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 | 8
 | C11 | 10n | Capacitor_SMD:C_0603_1608Metric | 0.17 | 1 | 0 | 10000pF ±10% 50V Ceramic Capacitor X7R 0603 (1608 Metric) | 445-5662-1-ND | https://www.digikey.com.au/product-detail/en/tdk-corporation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 | 8
 | C18 | 10n | Capacitor_SMD:C_0603_1608Metric | 0.17 | 1 | 0 | 10000pF ±10% 50V Ceramic Capacitor X7R 0603 (1608 Metric) | 445-5662-1-ND | https://www.digikey.com.au/product-detail/en/tdk-corporation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 | 8
 | C20 | 10n | Capacitor_SMD:C_0603_1608Metric | 0.17 | 1 | 0 | 10000pF ±10% 50V Ceramic Capacitor X7R 0603 (1608 Metric) | 445-5662-1-ND | https://www.digikey.com.au/product-detail/en/tdk-corporation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 | 8
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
